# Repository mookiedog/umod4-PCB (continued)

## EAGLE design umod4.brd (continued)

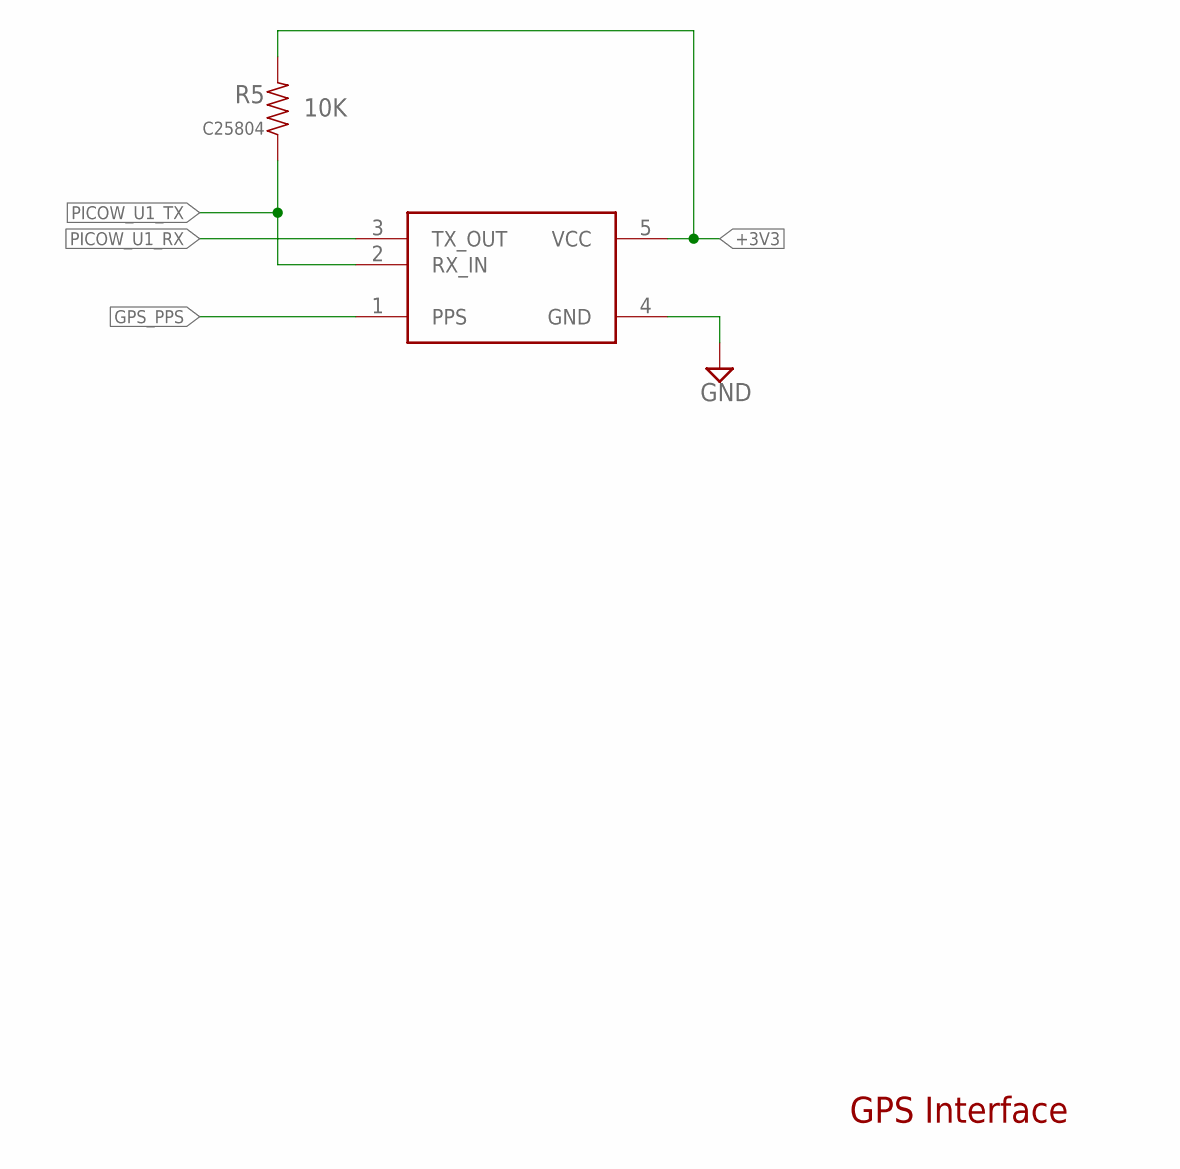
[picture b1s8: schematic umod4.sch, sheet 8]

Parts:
M1: Generic single-sided NEO-8; GPS-MODULE-DS
R5: 10K; SMD-0603-NOM; LCSC_PART C25804

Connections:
+3V3: M1.5 (VCC), R5.2; also elsewhere on the board
GND: M1.4 (GND); also elsewhere on the board
GPS_PPS: M1.1 (PPS); also elsewhere on the board
PICOW_U1_RX: M1.3 (TX_OUT); also elsewhere on the board
PICOW_U1_TX: M1.2 (RX_IN), R5.1; also elsewhere on the board

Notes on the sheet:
GPS Interface

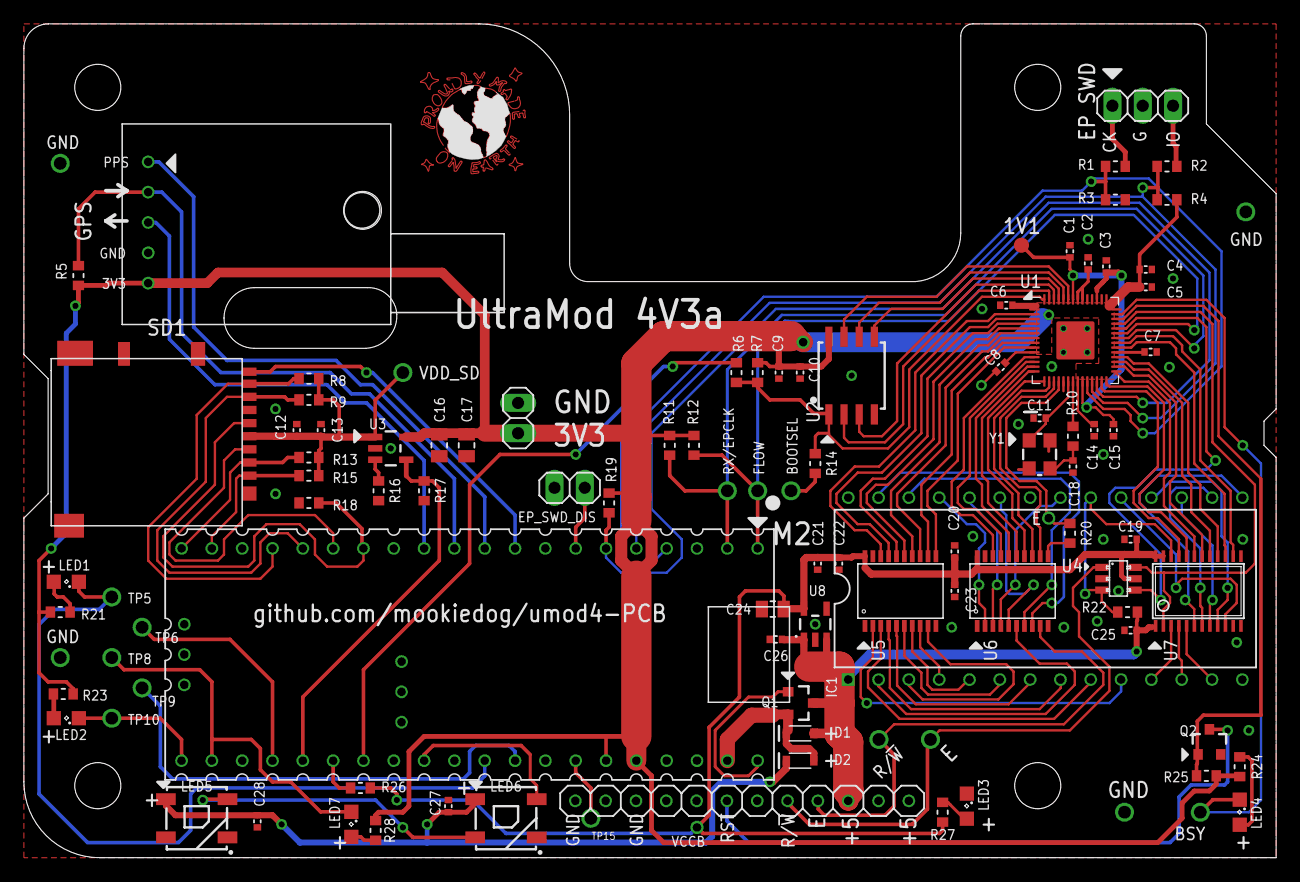
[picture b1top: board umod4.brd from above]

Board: 2 copper layers, 104.9 x 69.8 mm, 102 parts (0 on the bottom side), 110 nets.

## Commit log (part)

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2023-03-04 Initial commit of README and ChangeList
2023-03-04 Updates to README, Changelist, and design
2023-03-04 Added license file
2023-03-04 Cleanup
2023-03-25 New: 10-pin SWD, WS2812-2020, TestPlan doc
2023-03-26 Added WP squid pins
2023-03-26 Added thoughts on unswitched power supply
2023-04-02 Pullup Stops GPS From Disabling Its UART
2023-05-08 Updates after SD card testing
2023-05-08 Latest updates. See ChangeList.md.
2023-05-14 Power supply design updates
2023-05-17 Removed SD power switch
2023-05-20 Before rotating SPI connector
2023-05-21 Flipped J5 for easier hand soldering
2023-05-24 Updated all LSCS part attributes
2023-05-24 More updates to add LCSC part numbers
2023-05-31 Before renumbering components
2023-06-03 PCB Updates as per ChangeList.md
2023-06-18 Latest changes after github token changed
2023-06-18 Overvoltage Protection Thoughts
2024-12-29 Preparing for public release
2024-12-29 remove file with wrong case in name
2024-12-29 Fix filename case
2024-12-29 Doc updates before going public
2024-12-30 Updated debugger connections for WP, EP
2025-01-03 Power Supply Simplification
2025-01-04 Updating ChangeList.md with correct version
2025-01-04 Zip file should not be checked in
2025-01-04 Update current status in README
2025-01-04 Cleanup after using markdown lint
2025-01-07 All changes up to 4V1a fabrication
2025-01-08 Updates for 4V1 production
2025-03-03 Update 4V1 testing status
2025-04-14 New items added to 4V2 changelist
2025-04-19 Add to the 4V2 changelist
2025-05-17 Update changelist with potential approach for WS2812 EP status LED
2025-06-03 A few new ideas
2026-04-06 Updates for 4V2 work-in-progress
    - Latest version of 4V2 incorporating changes as per Changelist-4V2.md
2026-04-07 Fix CRLF line endings
